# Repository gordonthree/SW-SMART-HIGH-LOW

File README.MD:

# High / Low Smart Switch Node
* STM32G071 Microcontroller on board
* BTS50010 Profet Smart Switch for high side loads
* VNB35N07 OMNIFET Protected MOSFET for low side loads
* Microchip MCP1416 gate driver to ensure maximum low side efficiency
* Microchip MCP2562 isolated CAN bus transceiver
* Voltage divider to monitor supply voltage
* High side switch current monitoring and diagnostics
* Three position screw terminal block for CAN bus connection
* Heavy duty terminal block connectors for power in/out
* Headers for SWLINK programming and USART1 debug serial port

<IMG src="https://github.com/gordonthree/SW-SMART-HIGH-LOW/blob/main/SW-SMART-HIGH-LOW.png?raw=true" width=480>

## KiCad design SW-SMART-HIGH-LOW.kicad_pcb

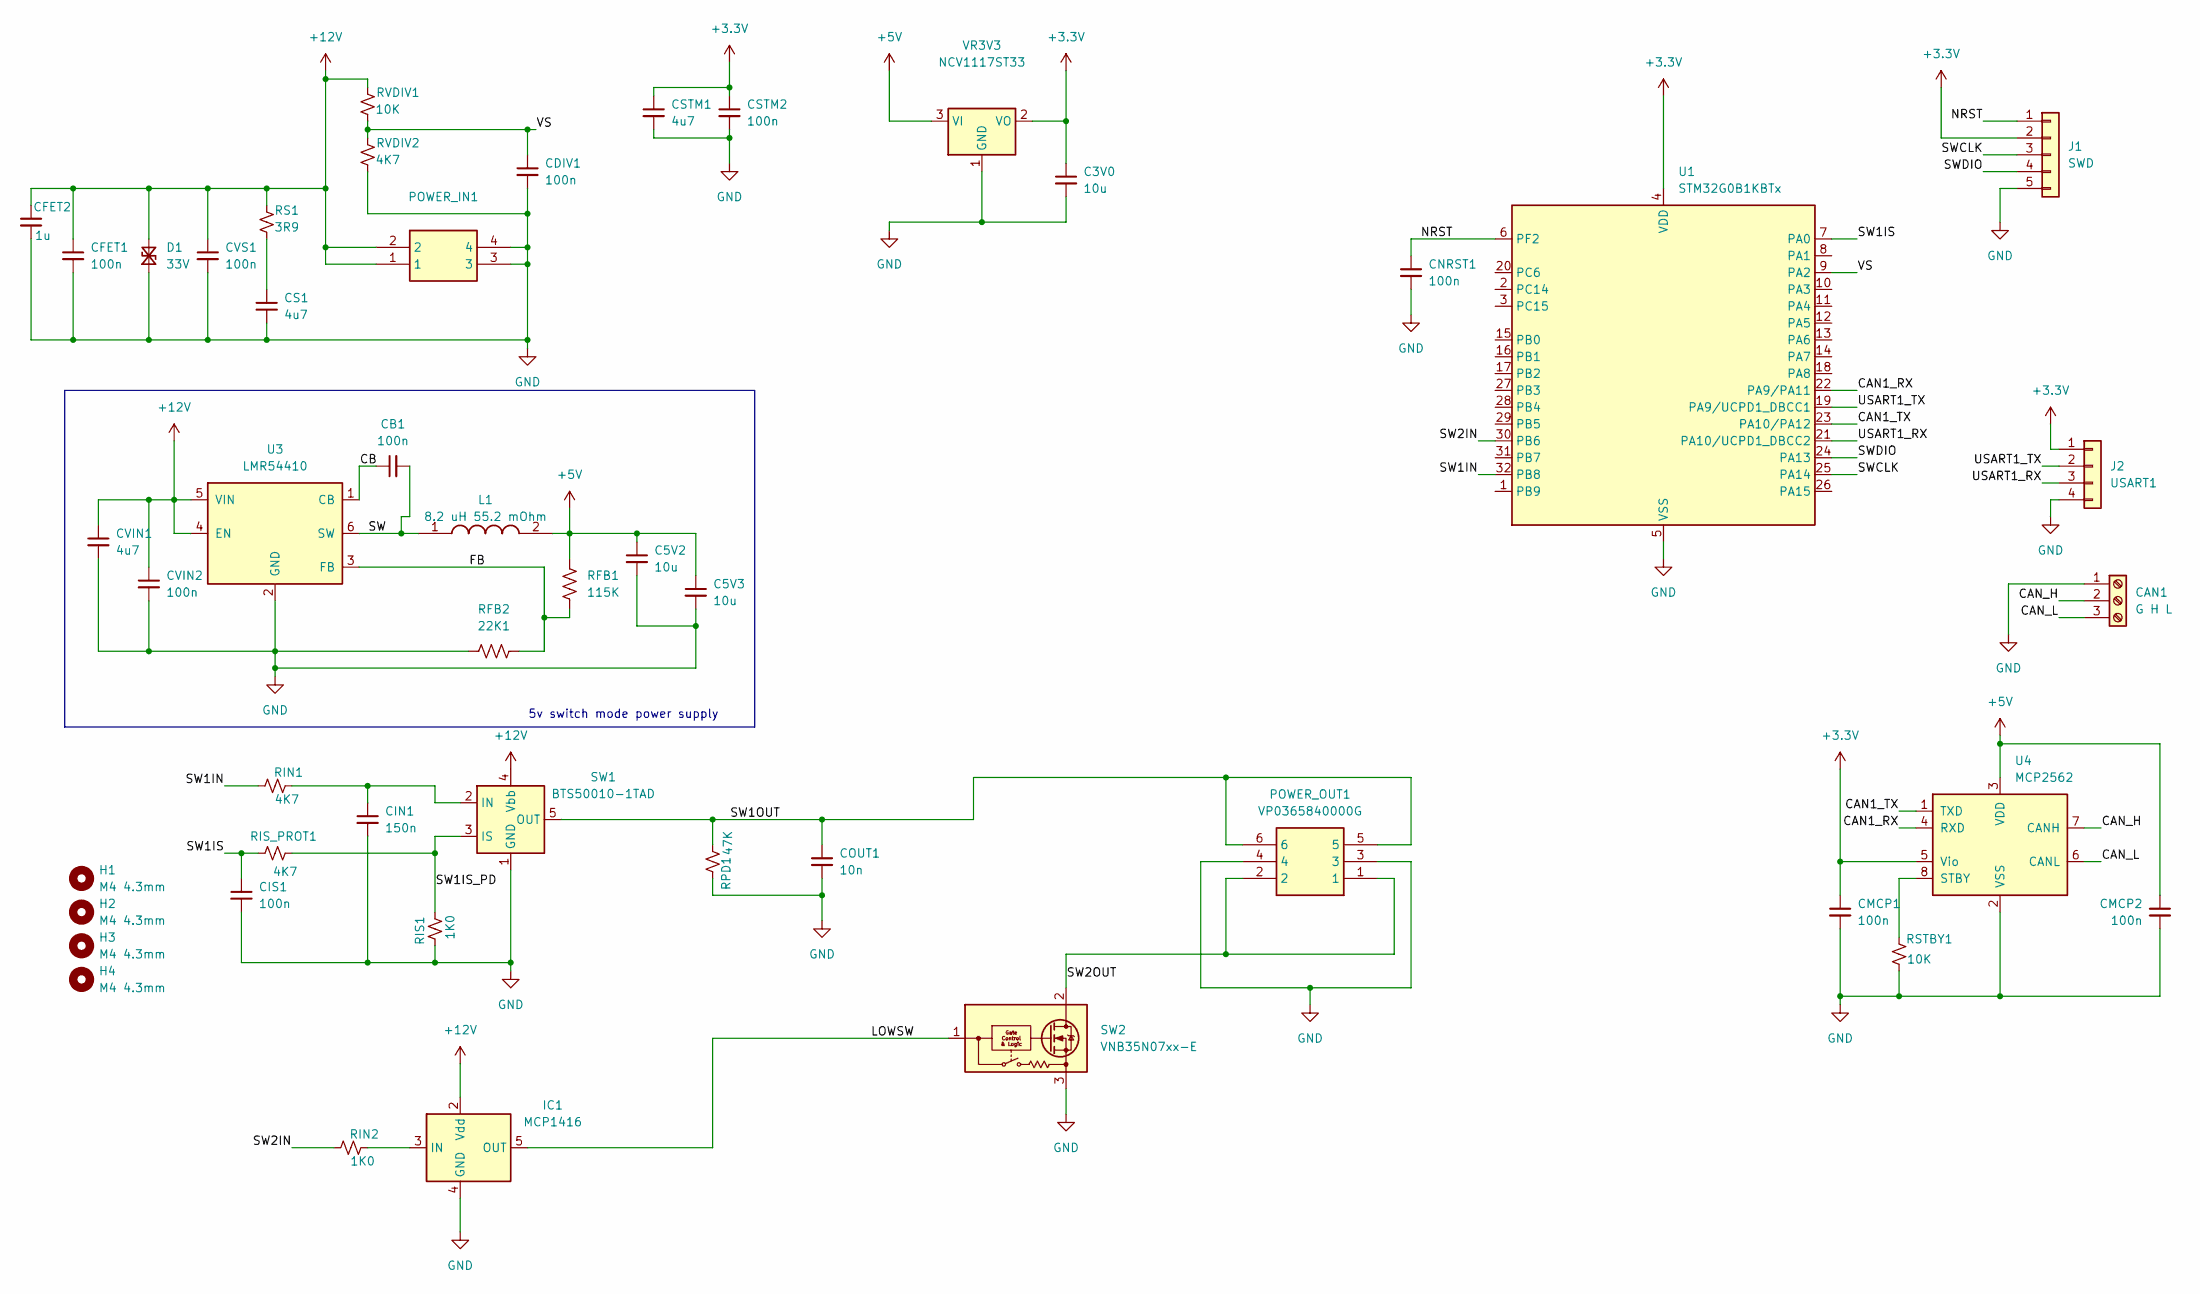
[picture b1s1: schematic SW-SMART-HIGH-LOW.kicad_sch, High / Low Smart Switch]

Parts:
C3V0, C5V2, C5V3: 10u; C_0805_2012Metric_Pad1.18x1.45mm_HandSolder
CAN1: G H L; TerminalBlock_Phoenix_MKDS-1,5-3-5.08_1x03_P5.08mm_Horizont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
CB1: 100n; C_0603_1608Metric_Pad1.08x0.95mm_HandSolder
CDIV1: 100n; C_0603_1608Metric_Pad1.08x0.95mm_HandSolder
CFET1: 100n; C_0603_1608Metric_Pad1.08x0.95mm_HandSolder
CFET2: 1u; C_0805_2012Metric_Pad1.18x1.45mm_HandSolder
CIN1: 150n; C_0603_1608Metric_Pad1.08x0.95mm_HandSolder
CIS1: 100n; C_0603_1608Metric_Pad1.08x0.95mm_HandSolder
CMCP1, CMCP2: 100n; C_0603_1608Metric_Pad1.08x0.95mm_HandSolder
CNRST1: 100n; C_0603_1608Metric_Pad1.08x0.95mm_HandSolder
COUT1: 10n; C_0603_1608Metric_Pad1.08x0.95mm_HandSolder
CS1: 4u7; C_0603_1608Metric_Pad1.08x0.95mm_HandSolder
CSTM1: 4u7; C_0805_2012Metric_Pad1.18x1.45mm_HandSolder
CSTM2: 100n; C_0603_1608Metric_Pad1.08x0.95mm_HandSolder
CVIN1: 4u7; C_1210_3225Metric_Pad1.33x2.70mm_HandSolder
CVIN2: 100n; C_0603_1608Metric_Pad1.08x0.95mm_HandSolder
CVS1: 100n; C_0603_1608Metric_Pad1.08x0.95mm_HandSolder
D1: 33V; D_SMA_Handsoldering
H1, H2, H3, H4: M4 4.3mm; MountingHole_4.3mm_M4
IC1: MCP1416; SOT-23-5
J1: SWD; 1x05_P2.54mm_Locking
J2: USART1; 1x04_P2.54mm_Locking
L1: 8.2 uH 55.2 mOhm; SRP5030HMT2R2M; Mouser Part Number SRP5030HMT-8R2M
POWER_IN1: PWRIN; VP0265840000G; Mouser Part Number 649-VP02658400J0G
POWER_OUT1: VP0365840000G; Mouser Part Number 649-VP03658400J0G
RFB1: 115K; R_0603_1608Metric_Pad0.98x0.95mm_HandSolder
RFB2: 22K1; R_0603_1608Metric_Pad0.98x0.95mm_HandSolder
RIN1: 4K7; R_0603_1608Metric_Pad0.98x0.95mm_HandSolder
RIN2: 1K0; R_0603_1608Metric_Pad0.98x0.95mm_HandSolder
RIS1: 1K0; R_0603_1608Metric_Pad0.98x0.95mm_HandSolder
RIS_PROT1: 4K7; R_0603_1608Metric_Pad0.98x0.95mm_HandSolder
RPD1: 47K; R_0603_1608Metric_Pad0.98x0.95mm_HandSolder
RS1: 3R9; R_0603_1608Metric_Pad0.98x0.95mm_HandSolder
RSTBY1: 10K; R_0603_1608Metric_Pad0.98x0.95mm_HandSolder
RVDIV1: 10K; R_0603_1608Metric_Pad0.98x0.95mm_HandSolder
RVDIV2: 4K7; R_0603_1608Metric_Pad0.98x0.95mm_HandSolder
SW1: BTS50010-1TAD; TO-263-7_TabPin4
SW2: VNB35N07xx-E; TO-263-2
U1: STM32G0B1KBTx; LQFP-32_7x7mm_P0.8mm
U3: LMR54410; SOT-23-6
U4: MCP2562; SOIC-8_3.9x4.9mm_P1.27mm
VR3V3: NCV1117ST33; SOT-223-3_TabPin2

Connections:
+3.3V: C3V0.1, CMCP1.1, CSTM1.1, CSTM2.1, J1.2, J2.1, U1.4 (VDD), U4.5 (Vio), VR3V3.2 (VO)
+5V: C5V2.1, C5V3.1, CMCP2.1, L1.2, RFB1.1, U4.3 (VDD), VR3V3.3 (VI)
+12V: CFET1.1, CFET2.1, CVIN1.1, CVIN2.1, CVS1.1, D1.2 (A2), IC1.2 (Vdd), POWER_IN1.1, POWER_IN1.2, RS1.2, RVDIV1.2, SW1.4 (Vbb), U3.4 (EN), U3.5 (VIN)
/CAN1_RX: U1.22 (PA9/PA11), U4.4 (RXD)
/CAN1_TX: U1.23 (PA10/PA12), U4.1 (TXD)
/CAN_H: CAN1.2, U4.7 (CANH)
/CAN_L: CAN1.3, U4.6 (CANL)
/CB: CB1.1, U3.1 (CB)
/FB: RFB1.2, RFB2.2, U3.3 (FB)
/LOWSW: IC1.5 (OUT), SW2.1 (INPUT)
/NRST: CNRST1.1, J1.1, U1.6 (PF2)
/SW: CB1.2, L1.1, U3.6 (SW)
/SW1IN: RIN1.1, U1.32 (PB8)
/SW1IS: CIS1.1, RIS_PROT1.1, U1.7 (PA0)
/SW1IS_PD: RIS1.2, RIS_PROT1.2, SW1.3 (IS)
/SW1OUT: COUT1.1, POWER_OUT1.5, POWER_OUT1.6, RPD1.2, SW1.5 (OUT), SW1.6 (OUT), SW1.7 (OUT)
/SW2IN: RIN2.1, U1.30 (PB6)
/SW2OUT: POWER_OUT1.1, POWER_OUT1.2, SW2.2 (DRAIN)
/SWCLK: J1.3, U1.25 (PA14)
/SWDIO: J1.4, U1.24 (PA13)
/USART1_RX: J2.3, U1.21 (PA10/UCPD1_DBCC2)
/USART1_TX: J2.2, U1.19 (PA9/UCPD1_DBCC1)
/VS: CDIV1.1, RVDIV1.1, RVDIV2.2, U1.9 (PA2)
GND: C3V0.2, C5V2.2, C5V3.2, CAN1.1, CDIV1.2, CFET1.2, CFET2.2, CIN1.2, CIS1.2, CMCP1.2, CMCP2.2, CNRST1.2, COUT1.2, CS1.2, CSTM1.2, CSTM2.2, CVIN1.2, CVIN2.2, CVS1.2, D1.1 (A1), IC1.4 (GND), J1.5, J2.4, POWER_IN1.3, POWER_IN1.4, POWER_OUT1.3, POWER_OUT1.4, RFB2.1, RIS1.1, RPD1.1, RSTBY1.1, RVDIV2.1, SW1.1 (GND), SW2.3 (SOURCE), U1.5 (VSS), U3.2 (GND), U4.2 (VSS), VR3V3.1 (GND)
unnamed: CS1.1, RS1.1
unnamed: IC1.3 (IN), RIN2.2
unnamed: CIN1.1, RIN1.2, SW1.2 (IN)
unnamed: RSTBY1.2, U4.8 (STBY)

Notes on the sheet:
5v switch mode power supply

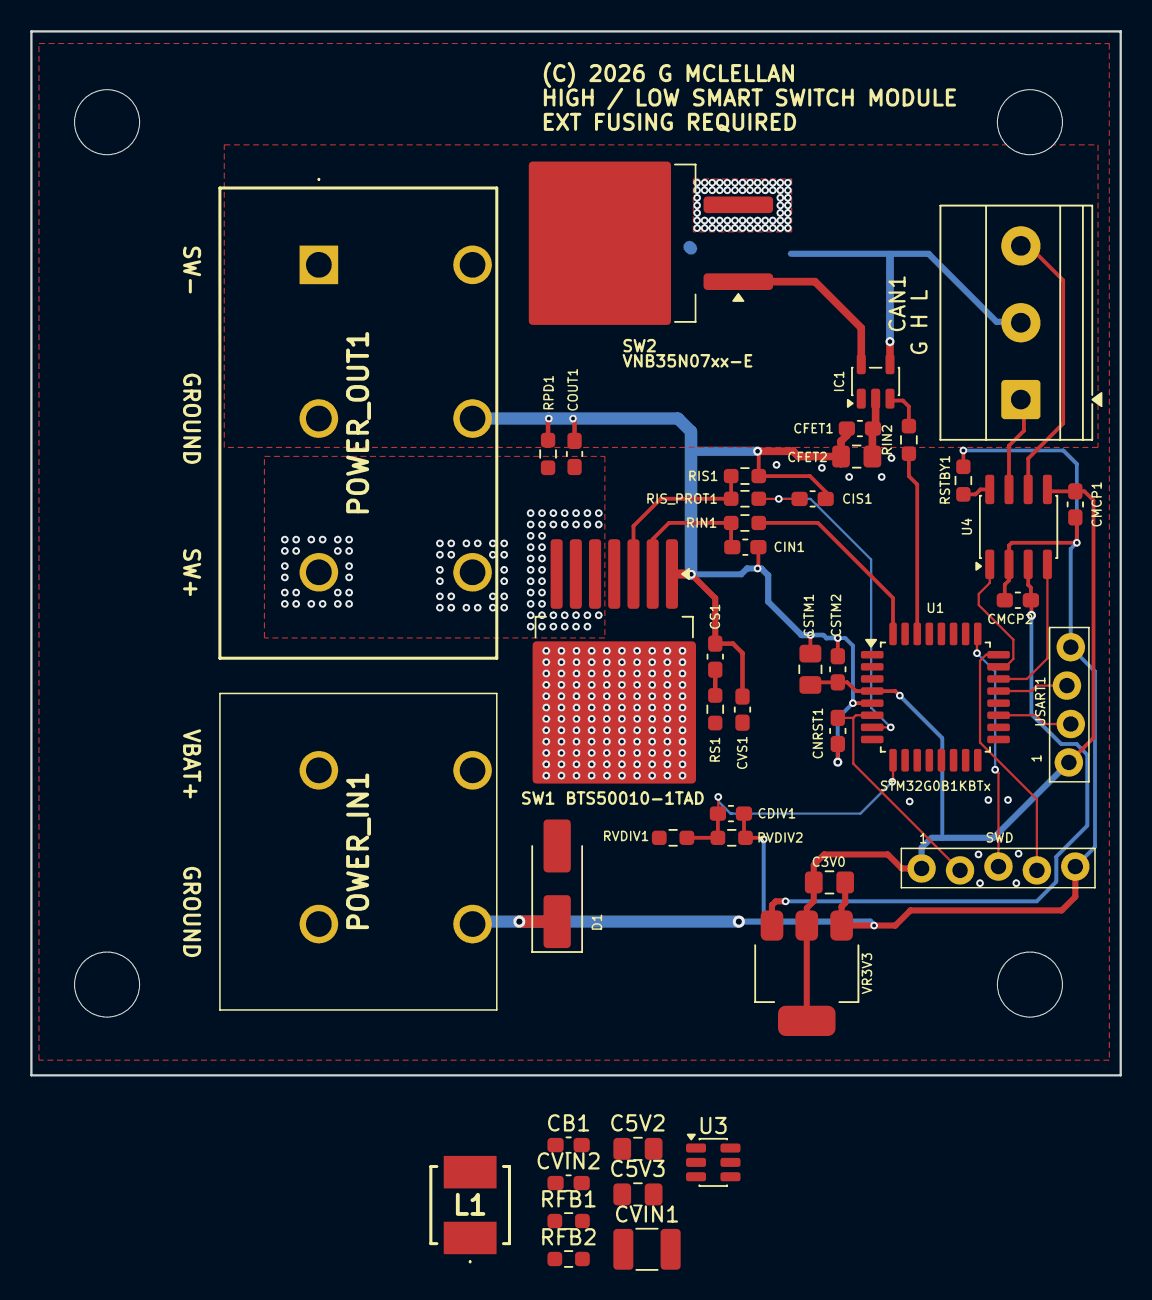
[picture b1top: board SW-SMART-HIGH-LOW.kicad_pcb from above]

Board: 2 copper layers, 72.0 x 69.0 mm, 48 parts (0 on the bottom side), 28 nets.

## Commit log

2026-01-19 project description
2026-01-19 rework schematic and pcb from similar project
2026-01-19 fit a lot of stuff onto a small board
2026-01-19 add 3d rendering
2026-01-19 making progress on the layout
2026-01-19 updated image url
2026-01-19 needs a bit more work
2026-01-19 silkscreen tweaks
2026-01-19 update rendering
2026-01-19 update image link
2026-01-19 add usart header
2026-01-19 fix pcb file issues caused by working across different dev machines
2026-01-19 updated rendering
2026-01-19 add silkscreen boxes around pin headers
2026-01-19 added voltage divider for +12v
2026-01-19 routing power and data nets
2026-01-19 ignore dupes folder
2026-01-19 I think the layout is complete
2026-01-19 update feature list
2026-01-19 clean up ground tracks
2026-01-19 drc check passed
2026-01-19 added caps for gate drive IC
2026-01-19 made some tracks wider
2026-01-19 passed drc
2026-01-30 added 5v smps, needs layout fixed now

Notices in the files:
SW-SMART-HIGH-LOW.kicad_pcb:
(C) 2026 G MCLELLAN
